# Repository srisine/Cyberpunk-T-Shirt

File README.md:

# Cyberpunk-T-Shirt
A futuristic T-Shirt inspired by cyberpunk 2077 which includes flexible small led boards on T-Shirt that can change colour based on user's body movement and also can be controlled by a phone.

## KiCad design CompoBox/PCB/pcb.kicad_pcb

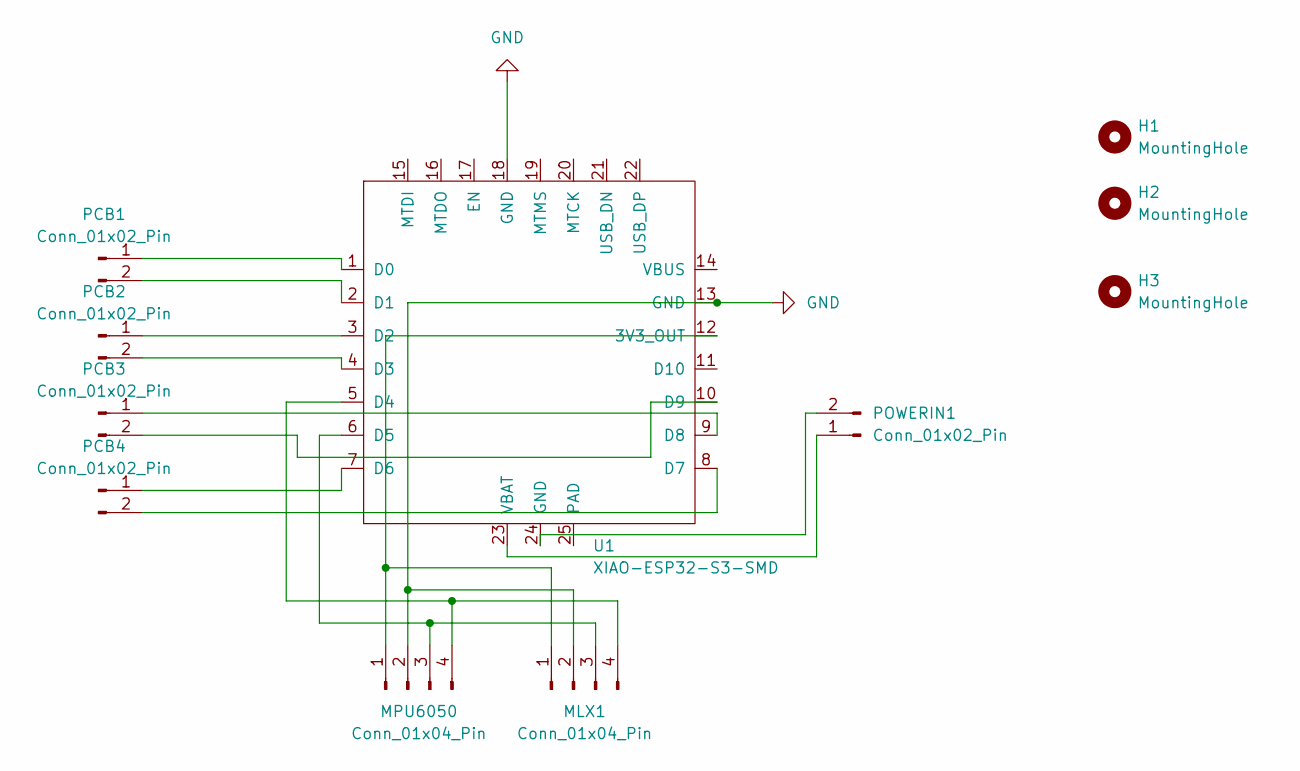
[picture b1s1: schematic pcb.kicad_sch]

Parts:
H1, H2, H3: MountingHole; MountingHole_3.2mm_M3
MLX1: Conn_01x04_Pin; PinHeader_1x04_P2.54mm_Vertical
MPU6050: Conn_01x04_Pin; PinHeader_1x04_P2.54mm_Vertical
PCB1, PCB2, PCB3, PCB4: Conn_01x02_Pin; PinHeader_1x02_P2.54mm_Vertical
POWERIN1: Conn_01x02_Pin; PinHeader_1x02_P2.54mm_Vertical
U1: XIAO-ESP32-S3-SMD

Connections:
GND: MLX1.2, MPU6050.2, U1.13 (GND), U1.18 (GND)
unnamed: MLX1.1, MPU6050.1, U1.12 (3V3_OUT)
unnamed: MLX1.3, MPU6050.3, U1.6 (D5)
unnamed: MLX1.4, MPU6050.4, U1.5 (D4)
unnamed: PCB1.1, U1.1 (D0)
unnamed: PCB1.2, U1.2 (D1)
unnamed: PCB2.1, U1.3 (D2)
unnamed: PCB2.2, U1.4 (D3)
unnamed: PCB3.1, U1.9 (D8)
unnamed: PCB3.2, U1.10 (D9)
unnamed: PCB4.1, U1.7 (D6)
unnamed: PCB4.2, U1.8 (D7)
unnamed: POWERIN1.1, U1.23 (VBAT)
unnamed: POWERIN1.2, U1.24 (GND)

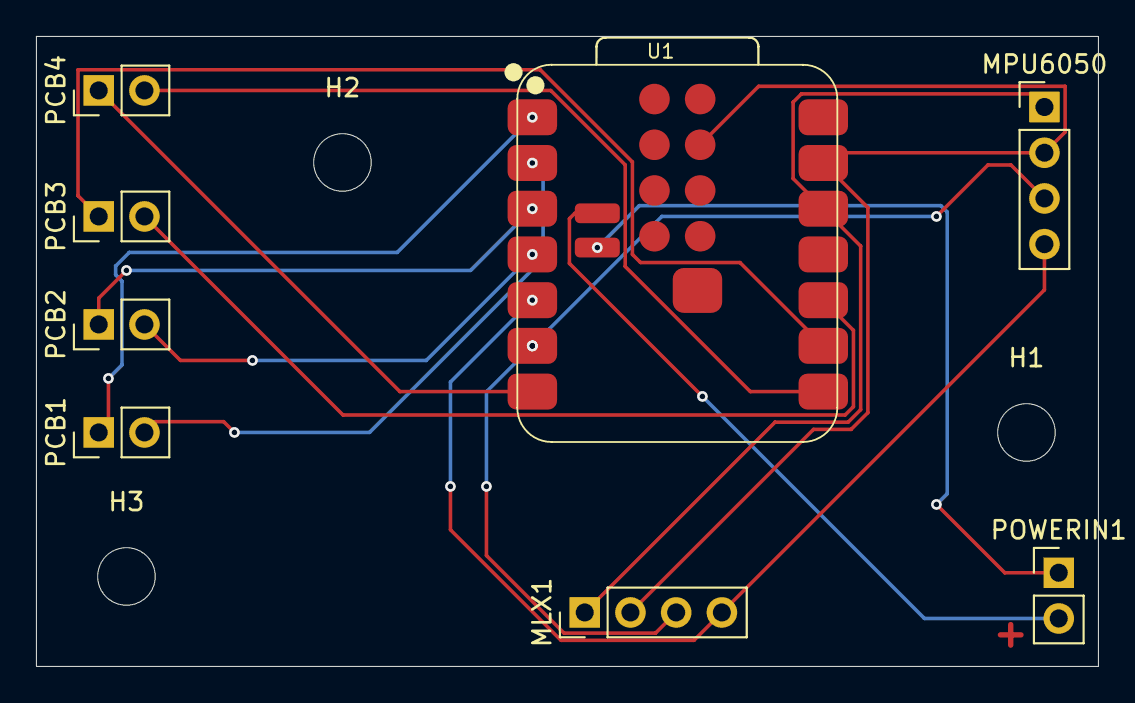
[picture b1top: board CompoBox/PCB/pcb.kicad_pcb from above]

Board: 2 copper layers, 59.0 x 35.0 mm, 11 parts (0 on the bottom side), 14 nets.

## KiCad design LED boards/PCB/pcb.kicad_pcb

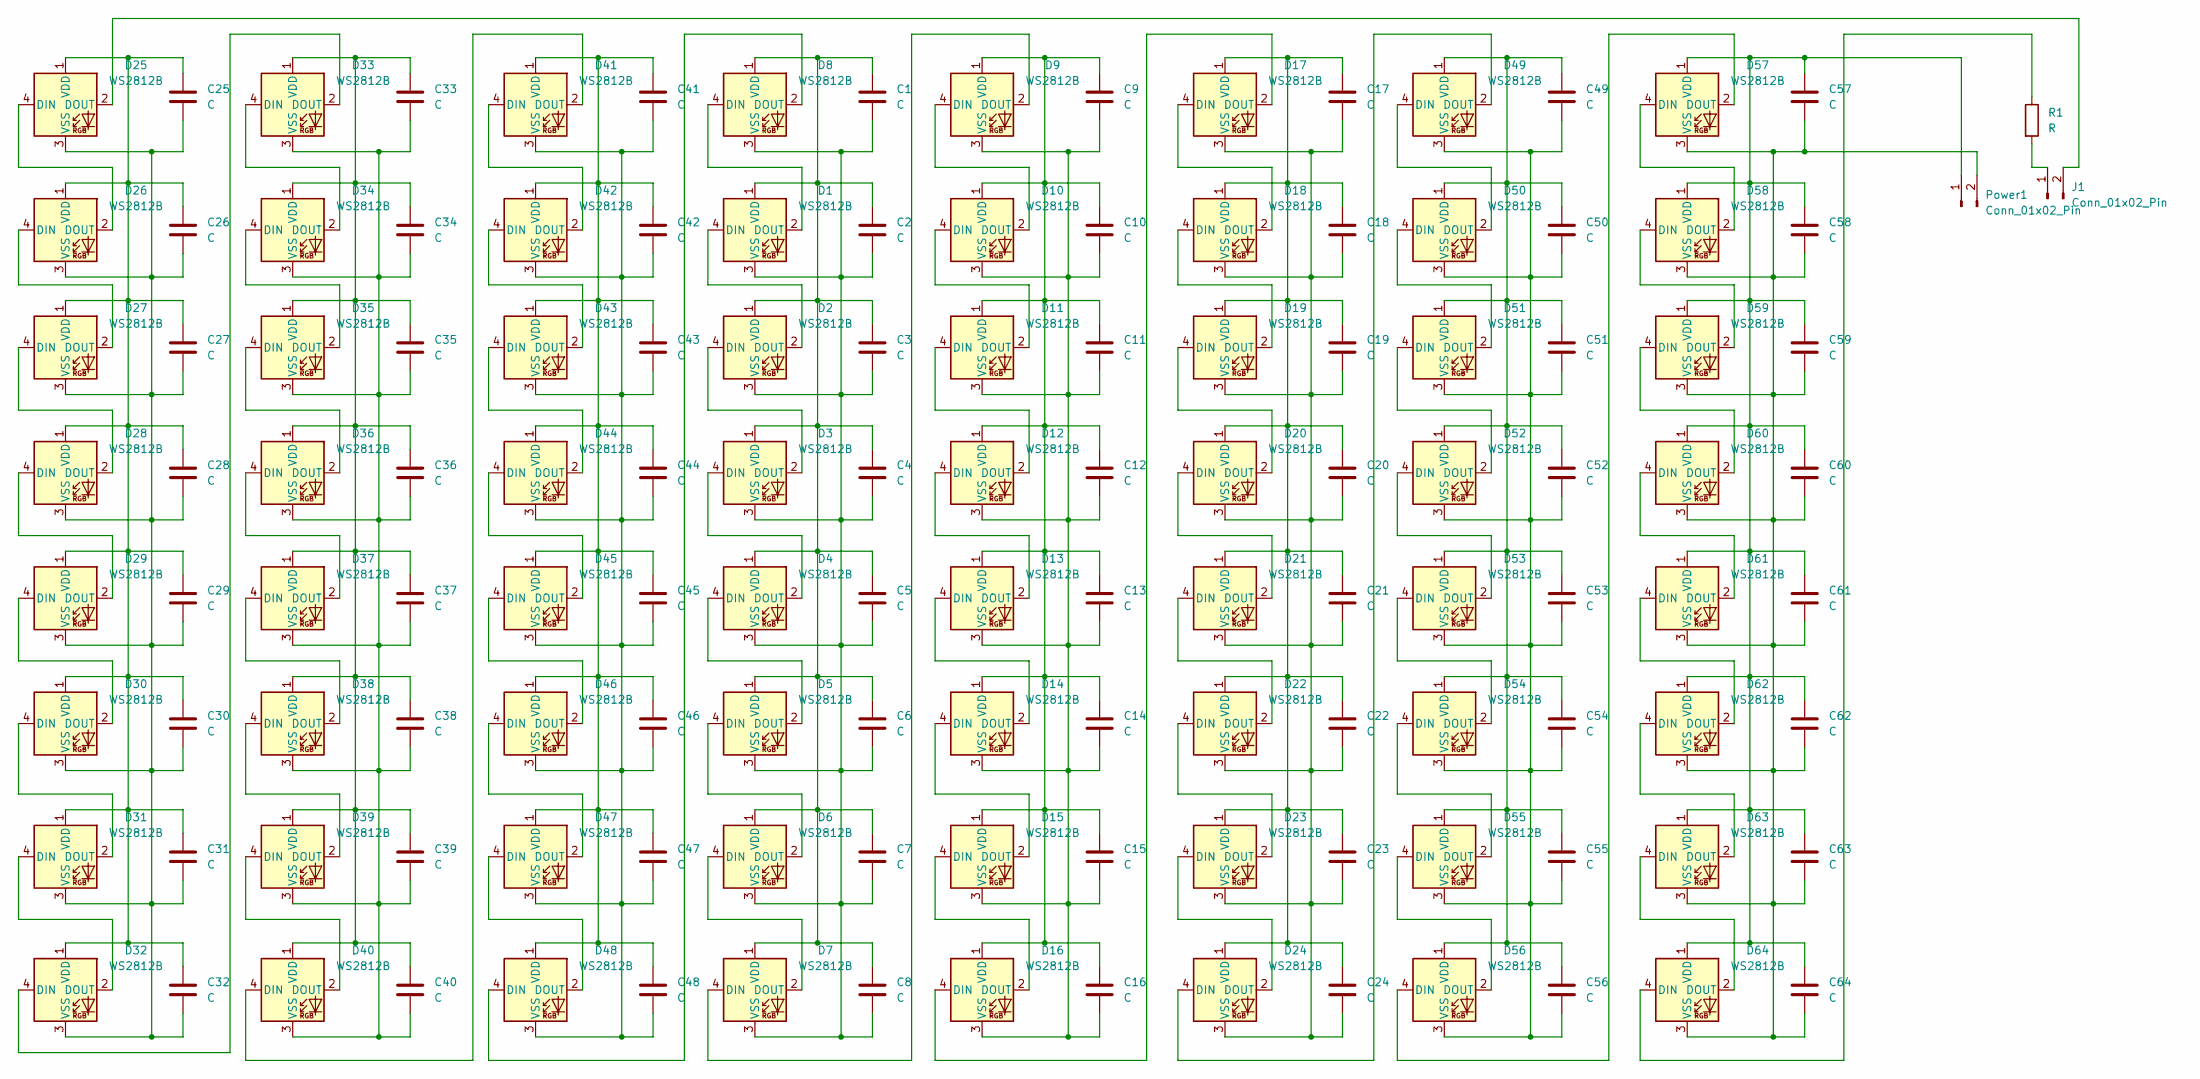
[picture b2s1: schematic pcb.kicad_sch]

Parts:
C1, C2, C3, C4, C5, C6, C7, C8, C9, C10, C11, C12, C13, C14, C15, C16, C17, C18, C19, C20, C21, C22, C23, C24, C25, C26, C27, C28, C29, C30, C31, C32, C33, C34, C35, C36, C37, C38, C39, C40, C41, C42, C43, C44, C45, C46, C47, C48, C49, C50, C51, C52, C53, C54, C55, C56, C57, C58, C59, C60, C61, C62, C63, C64: C; C_0603_1608Metric; LCSC C14663
D1, D2, D3, D4, D5, D6, D7, D8, D9, D10, D11, D12, D13, D14, D15, D16, D17, D18, D19, D20, D21, D22, D23, D24, D25, D26, D27, D28, D29, D30, D31, D32, D33, D34, D35, D36, D37, D38, D39, D40, D41, D42, D43, D44, D45, D46, D47, D48, D49, D50, D51, D52, D53, D54, D55, D56, D57, D58, D59, D60, D61, D62, D63, D64: WS2812B; LED_WS2812B_PLCC4_5.0x5.0mm_P3.2mm; LCSC C2761795
J1: Conn_01x02_Pin; PinHeader_1x02_P2.54mm_Vertical
Power1: Conn_01x02_Pin; PinHeader_1x02_P2.54mm_Vertical
R1: R; R_0603_1608Metric; LCSC C2286

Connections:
unnamed: D1.4 (DIN), D2.2 (DOUT)
unnamed: D1.2 (DOUT), D8.4 (DIN)
unnamed: C1.1, C2.1, C3.1, C4.1, C5.1, C6.1, C7.1, C8.1, D1.1 (VDD), D2.1 (VDD), D3.1 (VDD), D4.1 (VDD), D5.1 (VDD), D6.1 (VDD), D7.1 (VDD), D8.1 (VDD)
unnamed: C1.2, C2.2, C3.2, C4.2, C5.2, C6.2, C7.2, C8.2, D1.3 (VSS), D2.3 (VSS), D3.3 (VSS), D4.3 (VSS), D5.3 (VSS), D6.3 (VSS), D7.3 (VSS), D8.3 (VSS)
unnamed: D2.4 (DIN), D3.2 (DOUT)
unnamed: D3.4 (DIN), D4.2 (DOUT)
unnamed: D4.4 (DIN), D5.2 (DOUT)
unnamed: D5.4 (DIN), D6.2 (DOUT)
unnamed: D6.4 (DIN), D7.2 (DOUT)
unnamed: D7.4 (DIN), D9.2 (DOUT)
unnamed: D10.4 (DIN), D11.2 (DOUT)
unnamed: D9.4 (DIN), D10.2 (DOUT)
unnamed: C9.1, C10.1, C11.1, C12.1, C13.1, C14.1, C15.1, C16.1, D9.1 (VDD), D10.1 (VDD), D11.1 (VDD), D12.1 (VDD), D13.1 (VDD), D14.1 (VDD), D15.1 (VDD), D16.1 (VDD)
unnamed: C9.2, C10.2, C11.2, C12.2, C13.2, C14.2, C15.2, C16.2, D9.3 (VSS), D10.3 (VSS), D11.3 (VSS), D12.3 (VSS), D13.3 (VSS), D14.3 (VSS), D15.3 (VSS), D16.3 (VSS)
unnamed: D11.4 (DIN), D12.2 (DOUT)
unnamed: D12.4 (DIN), D13.2 (DOUT)
unnamed: D13.4 (DIN), D14.2 (DOUT)
unnamed: D14.4 (DIN), D15.2 (DOUT)
unnamed: D15.4 (DIN), D16.2 (DOUT)
unnamed: D16.4 (DIN), D17.2 (DOUT)
unnamed: D17.4 (DIN), D18.2 (DOUT)
unnamed: C17.1, C18.1, C19.1, C20.1, C21.1, C22.1, C23.1, C24.1, D17.1 (VDD), D18.1 (VDD), D19.1 (VDD), D20.1 (VDD), D21.1 (VDD), D22.1 (VDD), D23.1 (VDD), D24.1 (VDD)
unnamed: C17.2, C18.2, C19.2, C20.2, C21.2, C22.2, C23.2, C24.2, D17.3 (VSS), D18.3 (VSS), D19.3 (VSS), D20.3 (VSS), D21.3 (VSS), D22.3 (VSS), D23.3 (VSS), D24.3 (VSS)
unnamed: D18.4 (DIN), D19.2 (DOUT)
unnamed: D19.4 (DIN), D20.2 (DOUT)
unnamed: D20.4 (DIN), D21.2 (DOUT)
unnamed: D21.4 (DIN), D22.2 (DOUT)
unnamed: D22.4 (DIN), D23.2 (DOUT)
unnamed: D23.4 (DIN), D24.2 (DOUT)
unnamed: D24.4 (DIN), D49.2 (DOUT)
unnamed: D25.4 (DIN), D26.2 (DOUT)
unnamed: D25.2 (DOUT), J1.2
unnamed: C25.1, C26.1, C27.1, C28.1, C29.1, C30.1, C31.1, C32.1, D25.1 (VDD), D26.1 (VDD), D27.1 (VDD), D28.1 (VDD), D29.1 (VDD), D30.1 (VDD), D31.1 (VDD), D32.1 (VDD)
unnamed: C25.2, C26.2, C27.2, C28.2, C29.2, C30.2, C31.2, C32.2, D25.3 (VSS), D26.3 (VSS), D27.3 (VSS), D28.3 (VSS), D29.3 (VSS), D30.3 (VSS), D31.3 (VSS), D32.3 (VSS)
unnamed: D26.4 (DIN), D27.2 (DOUT)
unnamed: D27.4 (DIN), D28.2 (DOUT)
unnamed: D28.4 (DIN), D29.2 (DOUT)
unnamed: D29.4 (DIN), D30.2 (DOUT)
unnamed: D30.4 (DIN), D31.2 (DOUT)
unnamed: D31.4 (DIN), D32.2 (DOUT)
unnamed: D32.4 (DIN), D33.2 (DOUT)
unnamed: D33.4 (DIN), D34.2 (DOUT)
unnamed: C33.1, C34.1, C35.1, C36.1, C37.1, C38.1, C39.1, C40.1, D33.1 (VDD), D34.1 (VDD), D35.1 (VDD), D36.1 (VDD), D37.1 (VDD), D38.1 (VDD), D39.1 (VDD), D40.1 (VDD)
unnamed: C33.2, C34.2, C35.2, C36.2, C37.2, C38.2, C39.2, C40.2, D33.3 (VSS), D34.3 (VSS), D35.3 (VSS), D36.3 (VSS), D37.3 (VSS), D38.3 (VSS), D39.3 (VSS), D40.3 (VSS)
unnamed: D34.4 (DIN), D35.2 (DOUT)
unnamed: D35.4 (DIN), D36.2 (DOUT)
unnamed: D36.4 (DIN), D37.2 (DOUT)
unnamed: D37.4 (DIN), D38.2 (DOUT)
unnamed: D38.4 (DIN), D39.2 (DOUT)
unnamed: D39.4 (DIN), D40.2 (DOUT)
unnamed: D40.4 (DIN), D41.2 (DOUT)
unnamed: D41.4 (DIN), D42.2 (DOUT)
unnamed: C41.1, C42.1, C43.1, C44.1, C45.1, C46.1, C47.1, C48.1, D41.1 (VDD), D42.1 (VDD), D43.1 (VDD), D44.1 (VDD), D45.1 (VDD), D46.1 (VDD), D47.1 (VDD), D48.1 (VDD)
unnamed: C41.2, C42.2, C43.2, C44.2, C45.2, C46.2, C47.2, C48.2, D41.3 (VSS), D42.3 (VSS), D43.3 (VSS), D44.3 (VSS), D45.3 (VSS), D46.3 (VSS), D47.3 (VSS), D48.3 (VSS)
unnamed: D42.4 (DIN), D43.2 (DOUT)
unnamed: D43.4 (DIN), D44.2 (DOUT)
unnamed: D44.4 (DIN), D45.2 (DOUT)
unnamed: D45.4 (DIN), D46.2 (DOUT)
unnamed: D46.4 (DIN), D47.2 (DOUT)
unnamed: D47.4 (DIN), D48.2 (DOUT)
unnamed: D8.2 (DOUT), D48.4 (DIN)
unnamed: D49.4 (DIN), D50.2 (DOUT)
unnamed: C49.1, C50.1, C51.1, C52.1, C53.1, C54.1, C55.1, C56.1, D49.1 (VDD), D50.1 (VDD), D51.1 (VDD), D52.1 (VDD), D53.1 (VDD), D54.1 (VDD), D55.1 (VDD), D56.1 (VDD)
unnamed: C49.2, C50.2, C51.2, C52.2, C53.2, C54.2, C55.2, C56.2, D49.3 (VSS), D50.3 (VSS), D51.3 (VSS), D52.3 (VSS), D53.3 (VSS), D54.3 (VSS), D55.3 (VSS), D56.3 (VSS)
unnamed: D50.4 (DIN), D51.2 (DOUT)
unnamed: D51.4 (DIN), D52.2 (DOUT)
unnamed: D52.4 (DIN), D53.2 (DOUT)
unnamed: D53.4 (DIN), D54.2 (DOUT)
unnamed: D54.4 (DIN), D55.2 (DOUT)
unnamed: D55.4 (DIN), D56.2 (DOUT)
unnamed: D56.4 (DIN), D57.2 (DOUT)
unnamed: D57.4 (DIN), D58.2 (DOUT)
unnamed: C57.1, C58.1, C59.1, C60.1, C61.1, C62.1, C63.1, C64.1, D57.1 (VDD), D58.1 (VDD), D59.1 (VDD), D60.1 (VDD), D61.1 (VDD), D62.1 (VDD), D63.1 (VDD), D64.1 (VDD), Power1.1
unnamed: C57.2, C58.2, C59.2, C60.2, C61.2, C62.2, C63.2, C64.2, D57.3 (VSS), D58.3 (VSS), D59.3 (VSS), D60.3 (VSS), D61.3 (VSS), D62.3 (VSS), D63.3 (VSS), D64.3 (VSS), Power1.2
unnamed: D58.4 (DIN), D59.2 (DOUT)
unnamed: D59.4 (DIN), D60.2 (DOUT)
unnamed: D60.4 (DIN), D61.2 (DOUT)
unnamed: D61.4 (DIN), D62.2 (DOUT)
unnamed: D62.4 (DIN), D63.2 (DOUT)
unnamed: D63.4 (DIN), D64.2 (DOUT)
unnamed: D64.4 (DIN), R1.1
unnamed: J1.1, R1.2

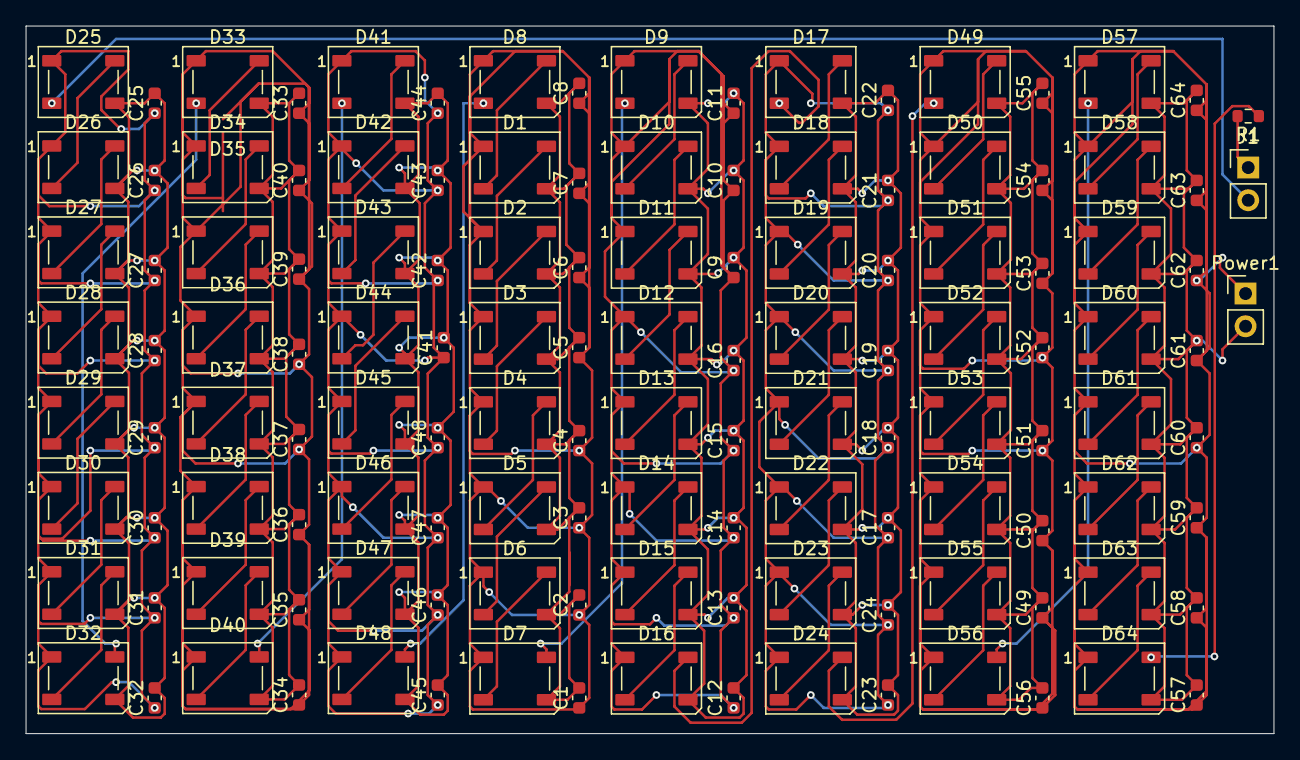
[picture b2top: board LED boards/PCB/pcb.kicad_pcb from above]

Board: 2 copper layers, 97.0 x 55.0 mm, 131 parts (0 on the bottom side), 82 nets.

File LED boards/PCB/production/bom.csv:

Designator,Footprint,Quantity,Value,LCSC Part #
"C1, C10, C11, C12, C13, C14, C15, C16, C17, C18, C19, C2, C20, C21, C22, C23, C24, C25, C26, C27, C28, C29, C3, C30, C31, C32, C33, C34, C35, C36, C37, C38, C39, C4, C40, C41, C42, C43, C44, C45, C46, C47, C48, C49, C5, C50, C51, C52, C53, C54, C55, C56, C57, C58, C59, C6, C60, C61, C62, C63, C64, C7, C8, C9",0603,64,C,C14663
"D1, D10, D11, D12, D13, D14, D15, D16, D17, D18, D19, D2, D20, D21, D22, D23, D24, D25, D26, D27, D28, D29, D3, D30, D31, D32, D33, D34, D35, D36, D37, D38, D39, D4, D40, D41, D42, D43, D44, D45, D46, D47, D48, D49, D5, D50, D51, D52, D53, D54, D55, D56, D57, D58, D59, D6, D60, D61, D62, D63, D64, D7, D8, D9",LED_WS2812B_PLCC4_5.0x5.0mm_P3.2mm,64,WS2812B,C2761795
"J1, POWER1",PinHeader_1x02_P2.54mm_Vertical,2,Conn_01x02_Pin,
R1,0603,1,R,C2286
